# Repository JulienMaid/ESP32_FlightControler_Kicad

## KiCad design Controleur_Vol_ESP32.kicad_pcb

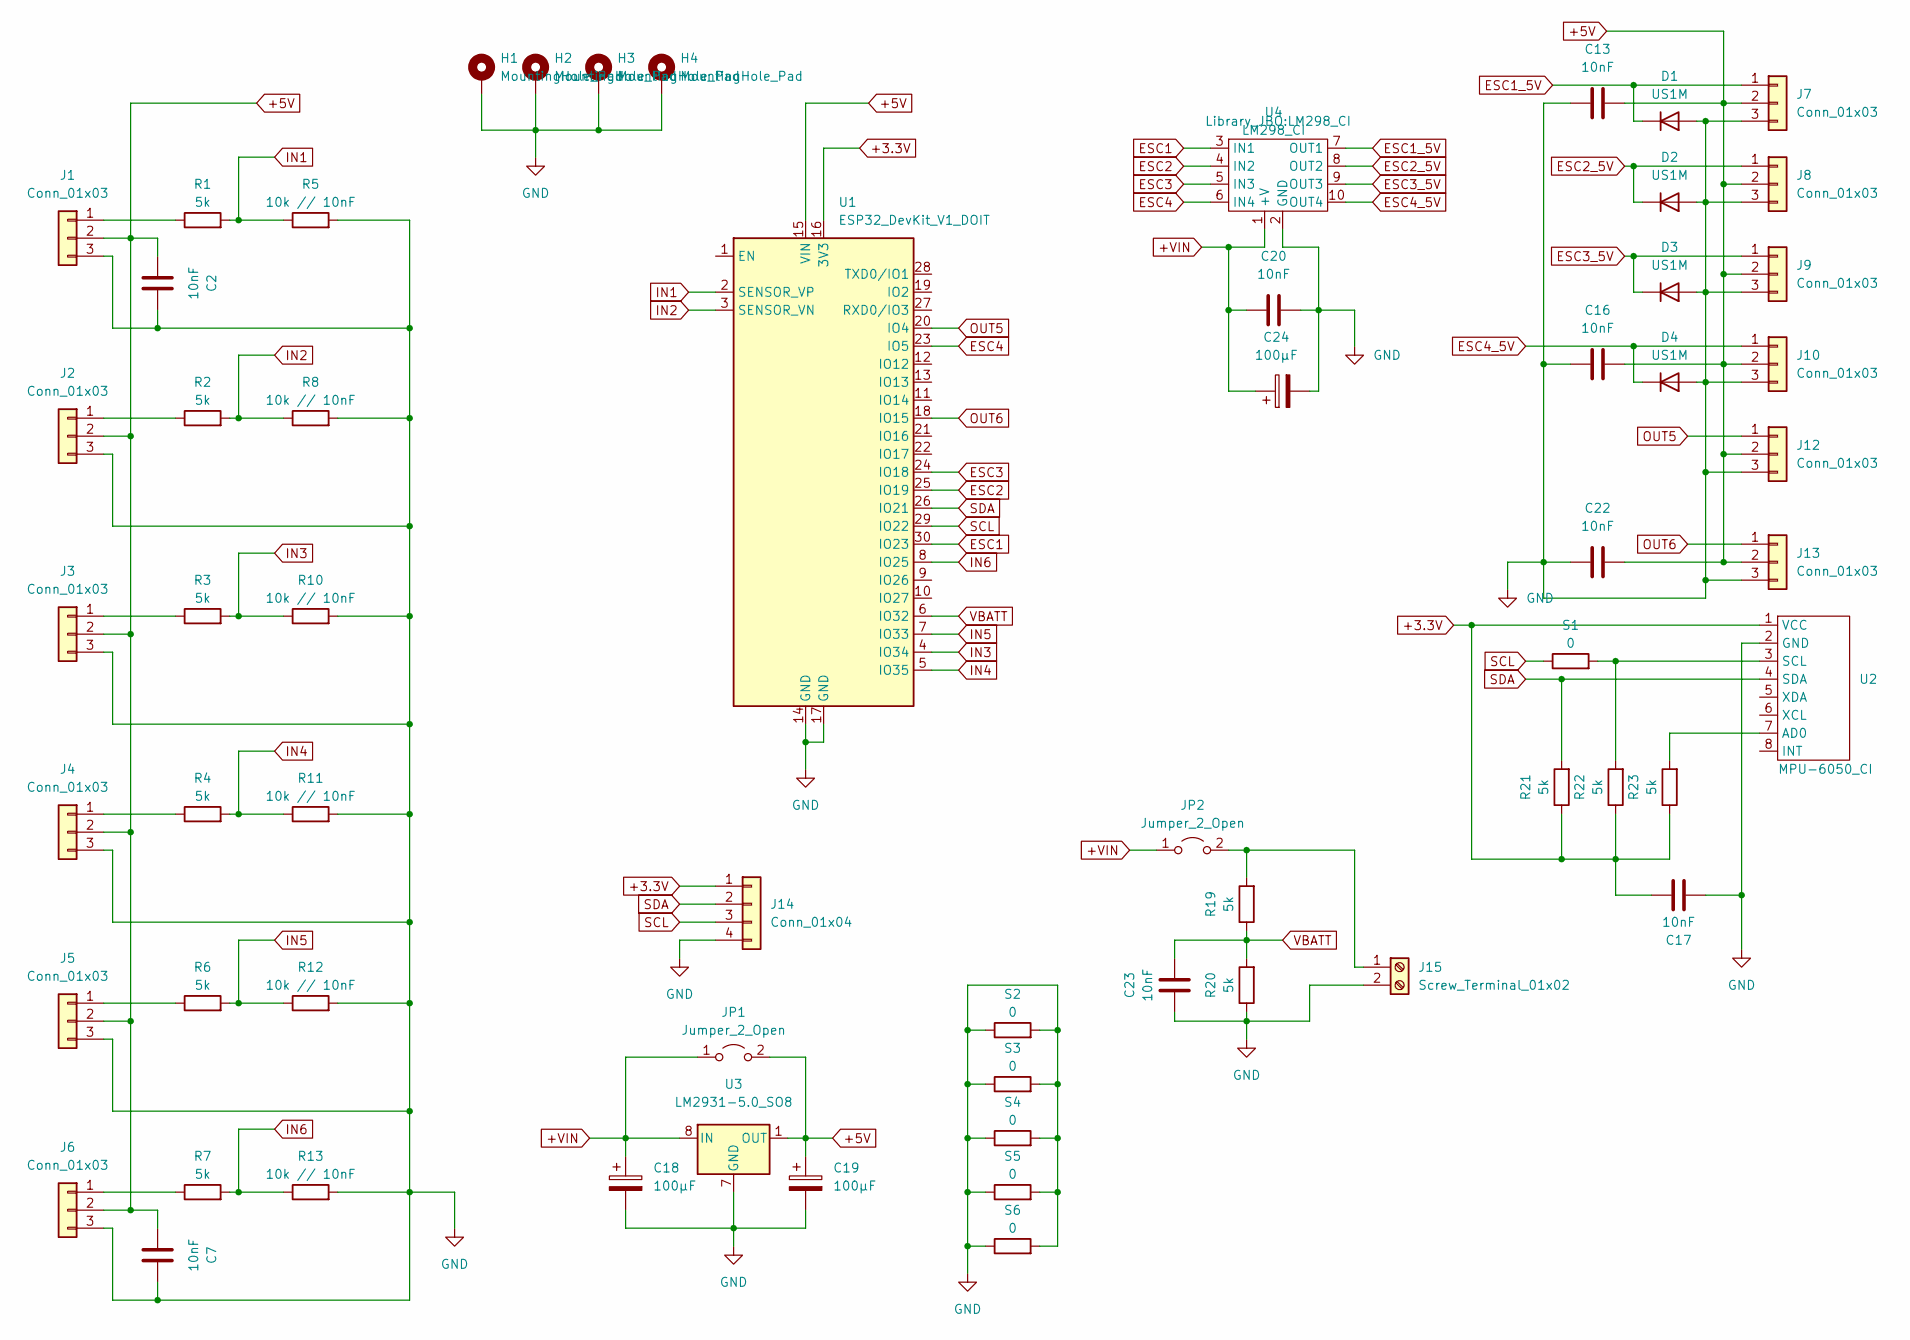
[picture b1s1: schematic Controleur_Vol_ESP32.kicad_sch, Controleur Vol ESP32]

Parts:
C2, C7, C13, C16, C17, C20, C22, C23: 10nF; C_1206_3216Metric_Pad1.33x1.80mm_HandSolder
C18, C19, C24: 100µF; CP_EIA-6032-20_AVX-F_Pad2.25x2.35mm_HandSolder
D1, D2, D3, D4: US1M; D_SMA
H1, H2, H3, H4: MountingHole_Pad; MountingHole_4.3mm_M4
J1, J2, J3, J4, J5, J6, J7, J8, J9, J10, J12, J13: Conn_01x03; PinHeader_1x03_P2.54mm_Vertical
J14: Conn_01x04; PinHeader_1x04_P2.54mm_Vertical
J15: Screw_Terminal_01x02; TerminalBlock_bornier-2_P5.08mm
JP1, JP2: Jumper_2_Open; PinHeader_1x02_P2.54mm_Vertical
R1, R2, R3, R4, R6, R7, R19, R20, R21, R22, R23: 5k; R_1206_3216Metric_Pad1.30x1.75mm_HandSolder
R5, R8, R10, R11, R12, R13: 10k // 10nF; R_1206_3216Metric_Pad1.30x1.75mm_HandSolder
S1, S2, S3, S4, S5, S6: 0; R_1206_3216Metric_Pad1.30x1.75mm_HandSolder
U1: ESP32_DevKit_V1_DOIT; esp32_devkit_v1_doit
U2: MPU-6050_CI
U3: LM2931-5.0_SO8; SOIC-8_3.9x4.9mm_P1.27mm
U4: LM298_CI

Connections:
+3.3V: C17.1, J14.1, R21.1, R22.1, R23.1, U1.16 (3V3), U2.1 (VCC)
+5V: C2.2, C7.2, C13.1, C16.1, C19.1, C22.1, J1.2, J2.2, J3.2, J4.2, J5.2, J6.2, J7.2, J8.2, J9.2, J10.2, J12.2, J13.2, JP1.2 (B), U1.15 (VIN), U3.1 (OUT)
+VIN: C18.1, C20.2, C24.1, JP1.1 (A), JP2.1 (A), U3.8 (IN), U4.1 (+V)
ESC1: U1.30 (IO23), U4.3 (IN1)
ESC1_5V: D1.1 (K), J7.1, U4.7 (OUT1)
ESC2: U1.25 (IO19), U4.4 (IN2)
ESC2_5V: D2.1 (K), J8.1, U4.8 (OUT2)
ESC3: U1.24 (IO18), U4.5 (IN3)
ESC3_5V: D3.1 (K), J9.1, U4.9 (OUT3)
ESC4: U1.23 (IO5), U4.6 (IN4)
ESC4_5V: D4.1 (K), J10.1, U4.10 (OUT4)
GND: C2.1, C7.1, C13.2, C16.2, C17.2, C18.2, C19.2, C20.1, C22.2, C23.1, C24.2, D1.2 (A), D2.2 (A), D3.2 (A), D4.2 (A), H1.1, H2.1, H3.1, H4.1, J1.3, J2.3, J3.3, J4.3, J5.3, J6.3, J7.3, J8.3, J9.3, J10.3, J12.3, J13.3, J14.4, J15.2, R5.2, R8.2, R10.2, R11.2, R12.2, R13.2, R20.1, S2.1, S2.2, S3.1, S3.2, S4.1, S4.2, S5.1, S5.2, S6.1, S6.2, U1.14 (GND), U1.17 (GND), U2.2 (GND), U3.2 (GND), U3.3 (GND), U3.6 (GND), U3.7 (GND), U4.2 (GND)
IN1: R1.2, R5.1, U1.2 (SENSOR_VP)
IN2: R2.2, R8.1, U1.3 (SENSOR_VN)
IN3: R3.2, R10.1, U1.4 (IO34)
IN4: R4.2, R11.1, U1.5 (IO35)
IN5: R6.2, R12.1, U1.7 (IO33)
IN6: R7.2, R13.1, U1.8 (IO25)
unnamed: J1.1, R1.1
unnamed: J2.1, R2.1
unnamed: J3.1, R3.1
unnamed: J4.1, R4.1
unnamed: J5.1, R6.1
unnamed: J6.1, R7.1
unnamed: J15.1, JP2.2 (B), R19.2
unnamed: R22.2, S1.2, U2.3 (SCL)
unnamed: R23.2, U2.7 (AD0)
OUT5: J12.1, U1.20 (IO4)
OUT6: J13.1, U1.18 (IO15)
SCL: J14.3, S1.1, U1.29 (IO22)
SDA: J14.2, R21.2, U1.26 (IO21), U2.4 (SDA)
VBATT: C23.2, R19.1, R20.2, U1.6 (IO32)

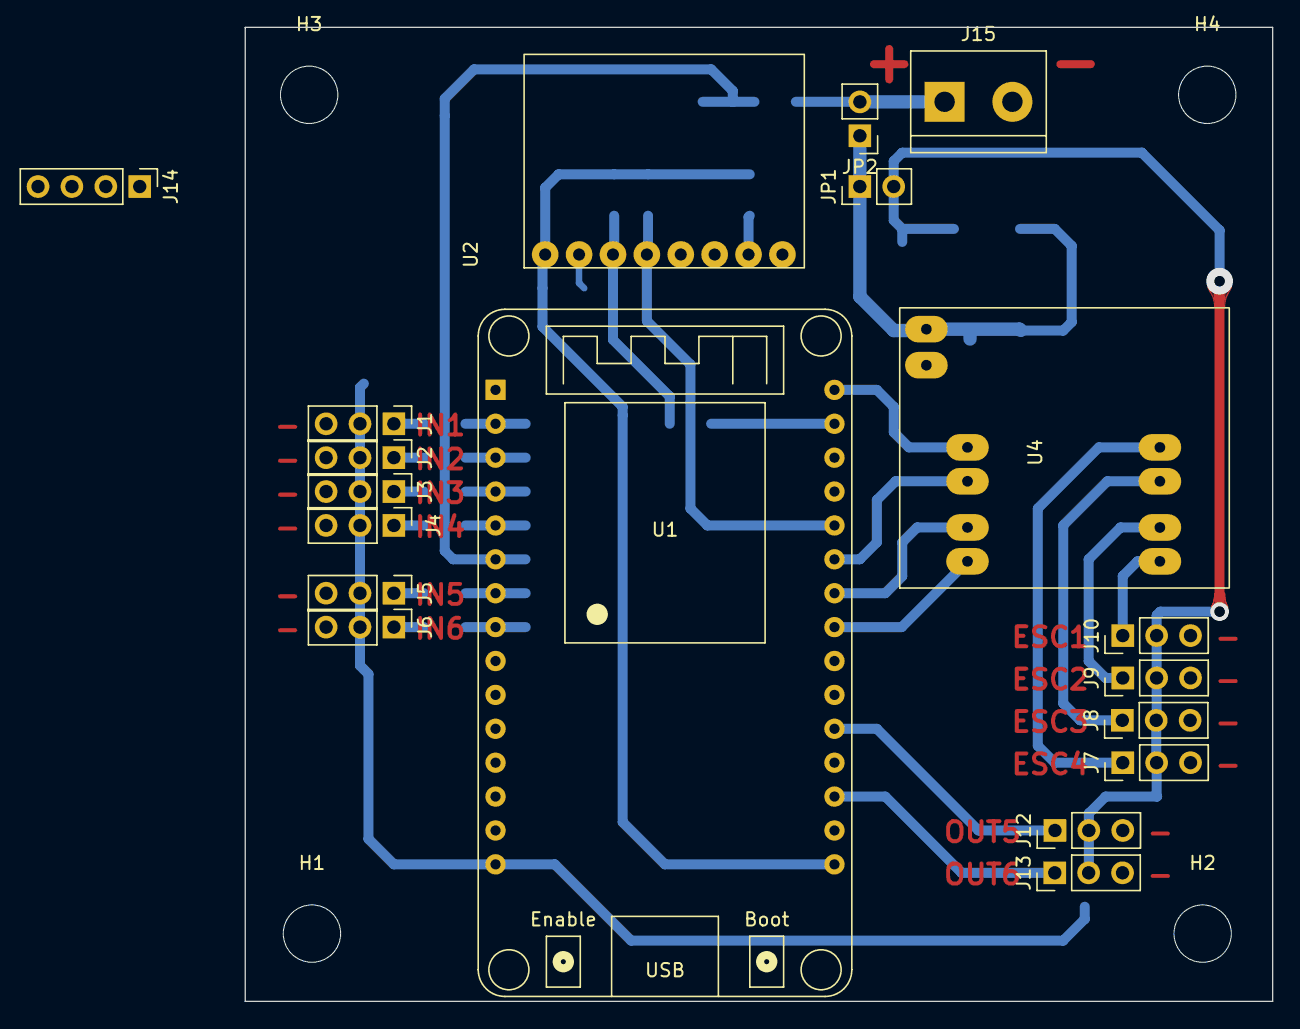
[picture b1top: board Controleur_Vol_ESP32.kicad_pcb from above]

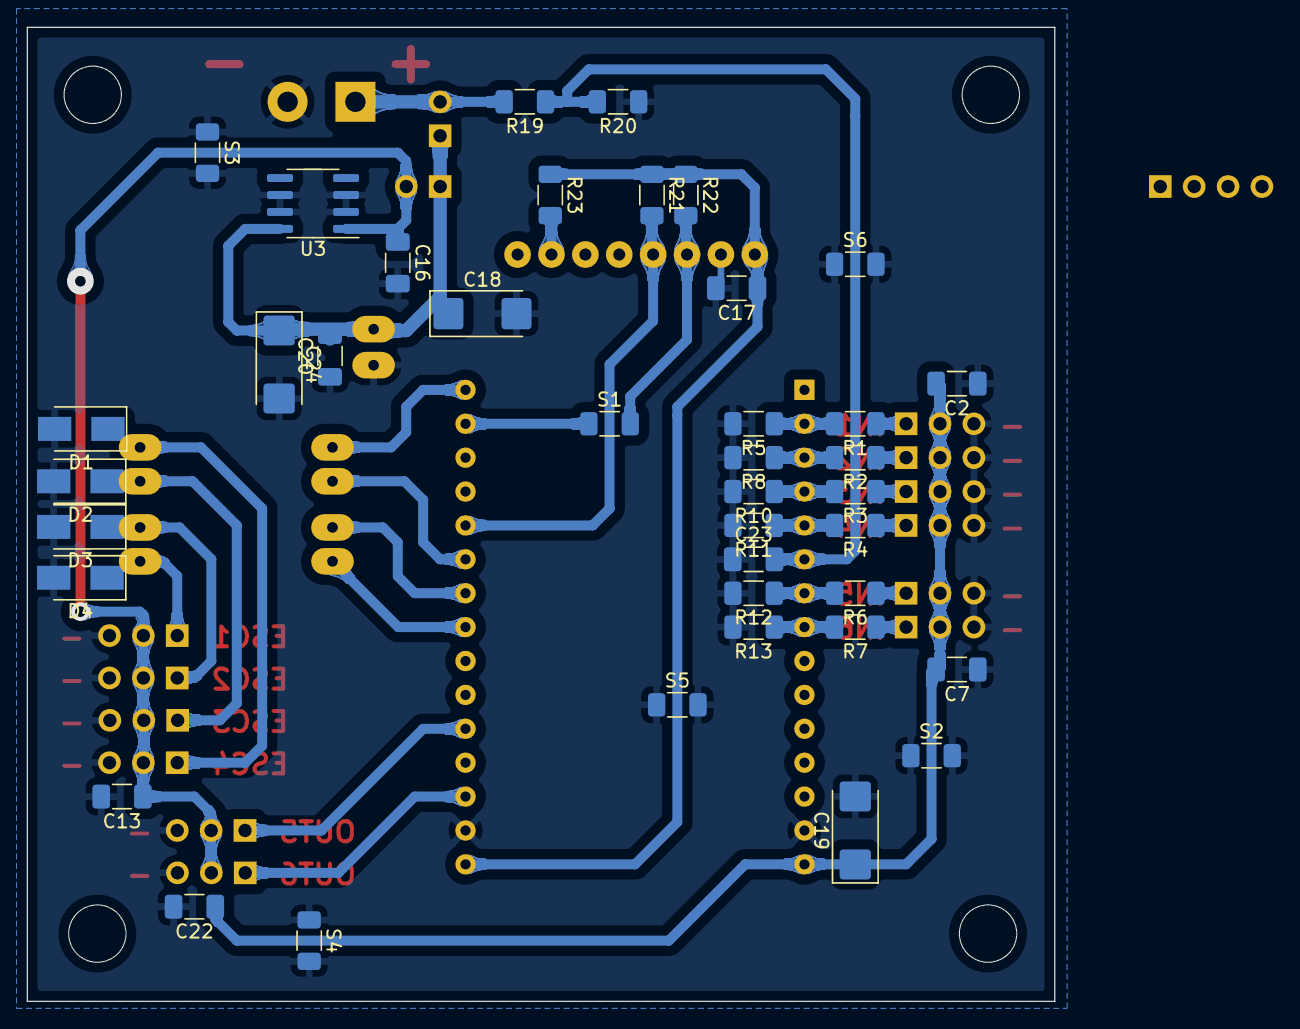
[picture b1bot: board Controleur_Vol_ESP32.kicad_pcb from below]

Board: 2 copper layers, 77.0 x 73.0 mm, 62 parts (39 on the bottom side), 32 nets.

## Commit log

2022-12-21 Création du dépot
2022-12-22 Ajout composants manquants sur schéma Assignation empreintes à tous les composants Ajout composant ESP32-devkit-v1 au projet
2022-12-23 Correction erreurs liens
2022-12-23 Ajout données cartouche
2023-01-01 Simplification schéma + MAJ lib symboles/empreintes
2023-01-01 Ajout trous de fixation
2023-01-01 1er jet de routage
2023-01-01 MAJ gitignore
2023-01-02 Ajout tearsdrop
2023-01-03 Straps maillage massage + contour PCB
2023-01-05 Ajout diodes "roue libre" sur sortie L293
2023-01-06 Ajout textes sur couche Top
